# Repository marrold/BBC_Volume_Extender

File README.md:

# BBC Volume Extender

A collection of PCBs for relocatin the volume control on a BBC Micro outside the case.

Currently incomplete

**Note:** Currently untested

## License

- This project is licensed under the MIT license

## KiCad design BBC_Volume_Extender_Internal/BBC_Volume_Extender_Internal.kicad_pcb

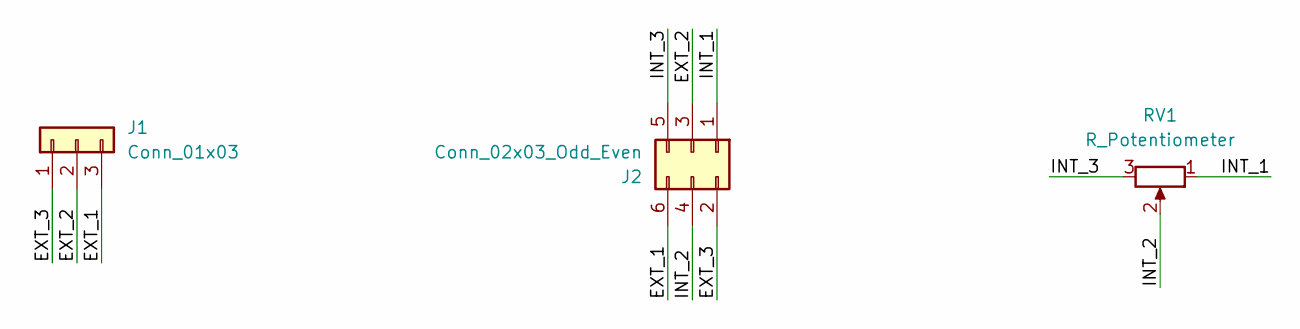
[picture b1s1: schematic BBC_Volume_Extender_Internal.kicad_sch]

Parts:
J1: Conn_01x03; PinHeader_1x03_P2.54mm_Vertical
J2: Conn_02x03_Odd_Even; PinHeader_2x03_P2.54mm_Vertical
RV1: R_Potentiometer; Potentiometer_Bourns_3386P_Vertical

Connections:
/EXT_1: J1.3, J2.6
/EXT_2: J1.2, J2.3
/EXT_3: J1.1, J2.2
/INT_1: J2.1, RV1.1
/INT_2: J2.4, RV1.2
/INT_3: J2.5, RV1.3

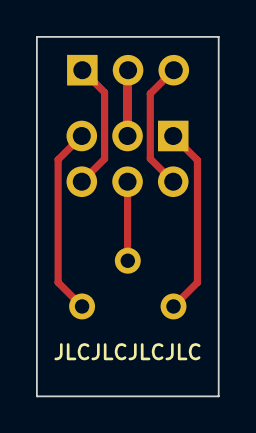
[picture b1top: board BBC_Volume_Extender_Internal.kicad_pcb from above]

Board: 2 copper layers, 10.1 x 20.0 mm, 3 parts (0 on the bottom side), 6 nets.

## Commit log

2024-01-24 init
